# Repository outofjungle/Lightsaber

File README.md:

# Lightsaber

## Wiring for the demo

The APA102 is 5V signaling. Please use appropriate logic level converter if working with 3.3V microcontrollers, like ESP8266 or ESP32. APA102 is controlled via the SPI bus.

| Lightsaber Pin | Microcontroller Pin |
|----------------|---------------------|
| GND            | GND                 |
| VCC            | 5V                  |
| CI             | SCK                 |
| DI             | MOSI                |

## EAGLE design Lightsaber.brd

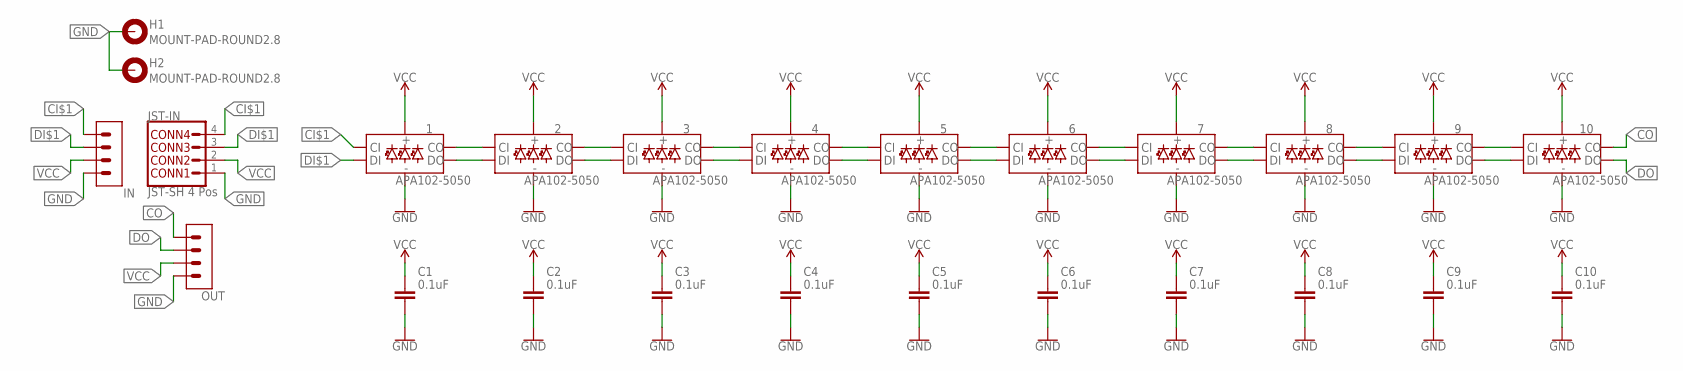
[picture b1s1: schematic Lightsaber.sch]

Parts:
1, 2, 3, 4, 5, 6, 7, 8, 9, 10: APA102-5050
C1, C2, C3, C4, C5, C6, C7, C8, C9, C10: 0.1uF; CAPC2012X110
H1, H2: MOUNT-PAD-ROUND2.8; 2,8-PAD
IN: 62000411121
JST-IN: JST-SH 4 Pos; JST04_1MM_VERT
OUT: 62000411121

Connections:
CI$1: 1.P2 (CI), IN.4, JST-IN.4
CI$2: 1.P5 (CO), 2.P2 (CI)
CI$3: 2.P5 (CO), 3.P2 (CI)
CI$4: 3.P5 (CO), 4.P2 (CI)
CI$5: 4.P5 (CO), 5.P2 (CI)
CI$6: 5.P5 (CO), 6.P2 (CI)
CI$7: 6.P5 (CO), 7.P2 (CI)
CI$8: 7.P5 (CO), 8.P2 (CI)
CI$9: 8.P5 (CO), 9.P2 (CI)
CI$10: 9.P5 (CO), 10.P2 (CI)
CO: 10.P5 (CO), OUT.4
DI$1: 1.P1 (DI), IN.3, JST-IN.3
DI$2: 1.P6 (DO), 2.P1 (DI)
DI$3: 2.P6 (DO), 3.P1 (DI)
DI$4: 3.P6 (DO), 4.P1 (DI)
DI$5: 4.P6 (DO), 5.P1 (DI)
DI$6: 5.P6 (DO), 6.P1 (DI)
DI$7: 6.P6 (DO), 7.P1 (DI)
DI$8: 7.P6 (DO), 8.P1 (DI)
DI$9: 8.P6 (DO), 9.P1 (DI)
DI$10: 9.P6 (DO), 10.P1 (DI)
DO: 10.P6 (DO), OUT.3
GND: 1.P3 (GND), 2.P3 (GND), 3.P3 (GND), 4.P3 (GND), 5.P3 (GND), 6.P3 (GND), 7.P3 (GND), 8.P3 (GND), 9.P3 (GND), 10.P3 (GND), C1.2, C2.2, C3.2, C4.2, C5.2, C6.2, C7.2, C8.2, C9.2, C10.2, H1.B2,8, H2.B2,8, IN.1, JST-IN.1, OUT.1
VCC: 1.P4 (VCC), 2.P4 (VCC), 3.P4 (VCC), 4.P4 (VCC), 5.P4 (VCC), 6.P4 (VCC), 7.P4 (VCC), 8.P4 (VCC), 9.P4 (VCC), 10.P4 (VCC), C1.1, C2.1, C3.1, C4.1, C5.1, C6.1, C7.1, C8.1, C9.1, C10.1, IN.2, JST-IN.2, OUT.2

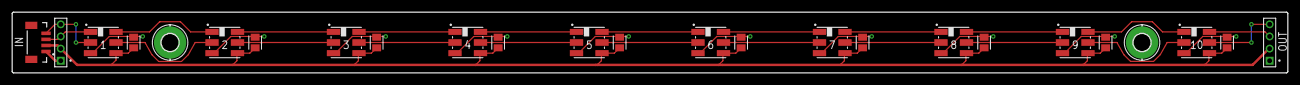
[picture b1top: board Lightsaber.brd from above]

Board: 2 copper layers, 210.0 x 10.0 mm, 25 parts (0 on the bottom side), 24 nets.

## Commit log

2021-04-21 Rounded corners
2021-04-22 fixed silkscreen for names/values
2021-04-22 added info labels to the silkscreen
2021-04-22 final fixes and gerber file generation
2021-04-22 added tented vias
2021-04-24 Fix ground trace width
2021-04-27 Adding demo using Adafruit huzzah ESP8266 MCU
2021-04-28 Added ATtiny85 support in code w/o seperate folder
2021-05-04 updated test code to cycle thru LEDs and colors
2021-05-04 fixed a hsv bug and minor improvements
2022-01-11 pushing uncommited changes

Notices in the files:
parts and their libraries:
SparkFun-LED: Licensing: Creative Commons ShareAlike 4.0 International - https://creativecommons.org/licenses/by-sa/4.0
